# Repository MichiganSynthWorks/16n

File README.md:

# 16n Fader Bank

Credits
Based on original work by Brian Crabtree and Sean Hellfritsch.
Minijack MIDI, I2C circuitry and CV outputs by Tom Armitage.
Firmware by Brian Crabtree, Tom Armitage, and Brendon Cassidy.

https://github.com/16n-faderbank/16n

License
=======

Code (AVR projects): GPL3.0.

Code: MIT license.

Hardware: cc-by-sa-4.0

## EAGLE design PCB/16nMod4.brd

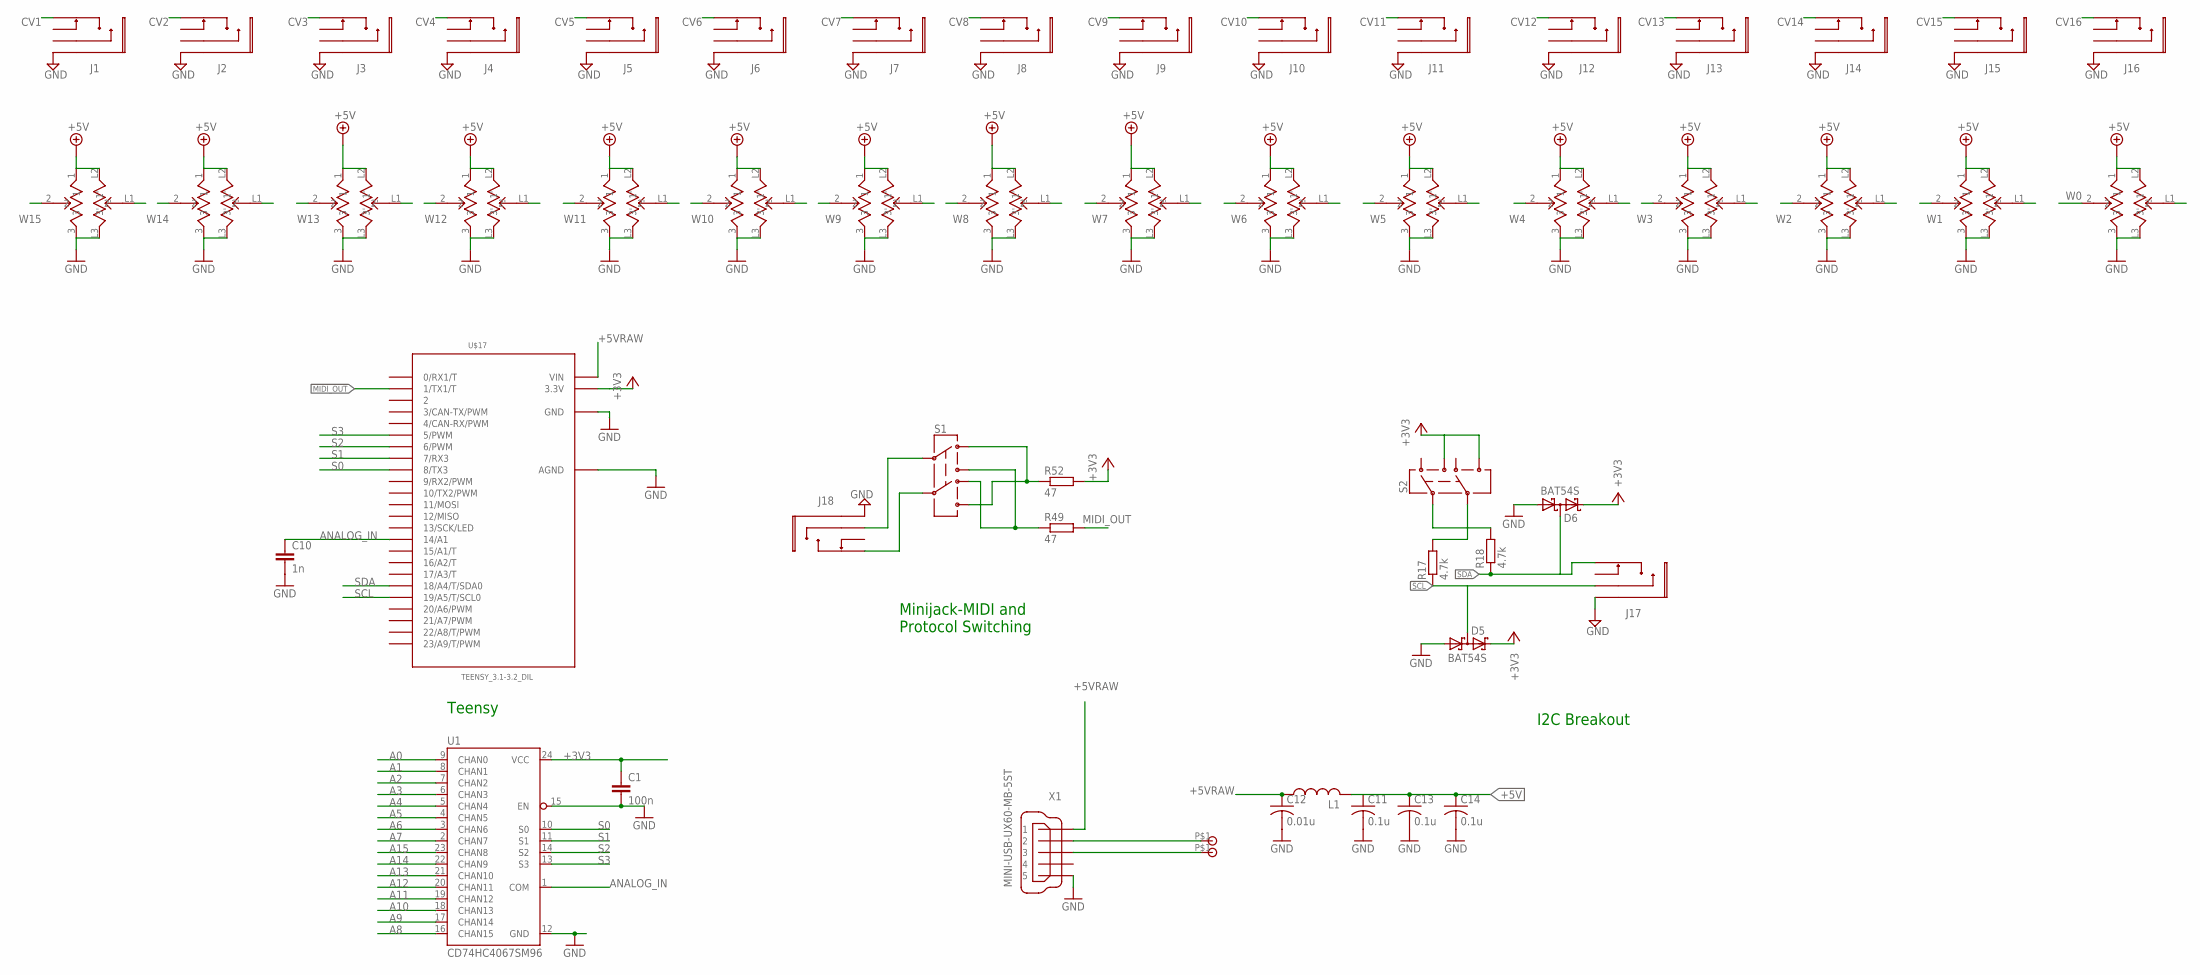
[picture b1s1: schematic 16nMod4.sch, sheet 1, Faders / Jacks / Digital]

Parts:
C1: 100n; C0805
C10: 1n; C0805
C11, C13, C14: 0.1u; C0805K
C12: 0.01u; C0805K
D5, D6: BAT54S; SOT23
J1, J2, J3, J4, J5, J6, J7, J8, J9, J10, J11, J12, J13, J14, J15, J16, J17, J18: PJ327E; PJ327
L1: L-USL2012C; L2012C
R17, R18: 4.7k; R0805
R49, R52: 47; R0805
S1, S2: SWITCH-DPDT; JS202011JAQN
U1: CD74HC4067SM96; SOIC127P1030X265-24
U$1, U$2, U$3, U$4, U$5, U$6, U$7, U$8, U$9, U$10, U$11, U$12, U$13, U$14, U$15, U$16: SLIDEPOT-ALPS-60MM; RS6011SP600
U$17: TEENSY_3.1-3.2_DIL; TEENSY_3.0-3.2&LC_DIL
U$19, U$20: POGO1X; POGO2MM
X1: MINI-USB-UX60-MB-5ST; UX60-MB-5ST

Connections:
+3V3: C1.1, D5.2, D6.2, R52.2, S2.P$3 (6), S2.P$7 (3), U1.24 (VCC), U$17.3.3V
+5V: C11.1, C13.1, C14.1, L1.2, U$1.1, U$1.L2 (1'), U$2.1, U$2.L2 (1'), U$3.1, U$3.L2 (1'), U$4.1, U$4.L2 (1'), U$5.1, U$5.L2 (1'), U$6.1, U$6.L2 (1'), U$7.1, U$7.L2 (1'), U$8.1, U$8.L2 (1'), U$9.1, U$9.L2 (1'), U$10.1, U$10.L2 (1'), U$11.1, U$11.L2 (1'), U$12.1, U$12.L2 (1'), U$13.1, U$13.L2 (1'), U$14.1, U$14.L2 (1'), U$15.1, U$15.L2 (1'), U$16.1, U$16.L2 (1'); also elsewhere on the board
+5VRAW: C12.1, L1.1, U$17.VIN, X1.1
A0: U1.9 (CHAN0); also elsewhere on the board
A1: U1.8 (CHAN1); also elsewhere on the board
A2: U1.7 (CHAN2); also elsewhere on the board
A3: U1.6 (CHAN3); also elsewhere on the board
A4: U1.5 (CHAN4); also elsewhere on the board
A5: U1.4 (CHAN5); also elsewhere on the board
A6: U1.3 (CHAN6); also elsewhere on the board
A7: U1.2 (CHAN7); also elsewhere on the board
A8: U1.16 (CHAN15); also elsewhere on the board
A9: U1.17 (CHAN14); also elsewhere on the board
A10: U1.18 (CHAN13); also elsewhere on the board
A11: U1.19 (CHAN12); also elsewhere on the board
A12: U1.20 (CHAN11); also elsewhere on the board
A13: U1.21 (CHAN10); also elsewhere on the board
A14: U1.22 (CHAN9); also elsewhere on the board
A15: U1.23 (CHAN8); also elsewhere on the board
ANALOG_IN: C10.1, U1.1 (COM), U$17.14/A0 (14/A1)
CV1: J1.P$2; also elsewhere on the board
CV2: J2.P$2; also elsewhere on the board
CV3: J3.P$2; also elsewhere on the board
CV4: J4.P$2; also elsewhere on the board
CV5: J5.P$2; also elsewhere on the board
CV6: J6.P$2; also elsewhere on the board
CV7: J7.P$2; also elsewhere on the board
CV8: J8.P$2; also elsewhere on the board
CV9: J9.P$2; also elsewhere on the board
CV10: J10.P$2; also elsewhere on the board
CV11: J11.P$2; also elsewhere on the board
CV12: J12.P$2; also elsewhere on the board
CV13: J13.P$2; also elsewhere on the board
CV14: J14.P$2; also elsewhere on the board
CV15: J15.P$2; also elsewhere on the board
CV16: J16.P$2; also elsewhere on the board
D+: U$20.P$1, X1.3
D-: U$19.P$1, X1.2
GND: C1.2, C10.2, C11.2, C12.2, C13.2, C14.2, D5.3 (1), D6.3 (1), J1.P$1, J2.P$1, J3.P$1, J4.P$1, J5.P$1, J6.P$1, J7.P$1, J8.P$1, J9.P$1, J10.P$1, J11.P$1, J12.P$1, J13.P$1, J14.P$1, J15.P$1, J16.P$1, J17.P$1, J18.P$1, U1.12 (GND), U1.15 (EN), U$1.3, U$1.L3 (3'), U$2.3, U$2.L3 (3'), U$3.3, U$3.L3 (3'), U$4.3, U$4.L3 (3'), U$5.3, U$5.L3 (3'), U$6.3, U$6.L3 (3'), U$7.3, U$7.L3 (3'), U$8.3, U$8.L3 (3'), U$9.3, U$9.L3 (3'), U$10.3, U$10.L3 (3'), U$11.3, U$11.L3 (3'), U$12.3, U$12.L3 (3'), U$13.3, U$13.L3 (3'), U$14.3, U$14.L3 (3'), U$15.3, U$15.L3 (3'), U$16.3, U$16.L3 (3'), U$17.AGND, U$17.GND, X1.5; also elsewhere on the board
MIDI_OUT: R49.2, U$17.1 (1/TX1/T)
unnamed: J18.P$2, S1.P$2 (5)
unnamed: J18.P$3, S1.P$6 (2)
unnamed: R49.1, S1.P$1 (4), S1.P$7 (3)
unnamed: R52.1, S1.P$3 (6), S1.P$5 (1)
unnamed: R17.2, S2.P$2 (5)
unnamed: R18.2, S2.P$6 (2)
S0: U1.10 (S0), U$17.8 (8/TX3)
S1: U1.11 (S1), U$17.7 (7/RX3)
S2: U1.14 (S2), U$17.6 (6/PWM)
S3: U1.13 (S3), U$17.5 (5/PWM)
SCL: D5.1 (3), J17.P$3, R17.1, U$17.19/A5 (19/A5/T/SCL0)
SDA: D6.1 (3), J17.P$2, R18.1, U$17.18/A4 (18/A4/T/SDA0)
W0: U$1.2, U$1.L1 (2'); also elsewhere on the board
W1: U$2.2, U$2.L1 (2'); also elsewhere on the board
W2: U$3.2, U$3.L1 (2'); also elsewhere on the board
W3: U$4.2, U$4.L1 (2'); also elsewhere on the board
W4: U$5.2, U$5.L1 (2'); also elsewhere on the board
W5: U$6.2, U$6.L1 (2'); also elsewhere on the board
W6: U$7.2, U$7.L1 (2'); also elsewhere on the board
W7: U$8.2, U$8.L1 (2'); also elsewhere on the board
W8: U$9.2, U$9.L1 (2'); also elsewhere on the board
W9: U$10.2, U$10.L1 (2'); also elsewhere on the board
W10: U$11.2, U$11.L1 (2'); also elsewhere on the board
W11: U$12.2, U$12.L1 (2'); also elsewhere on the board
W12: U$13.2, U$13.L1 (2'); also elsewhere on the board
W13: U$14.2, U$14.L1 (2'); also elsewhere on the board
W14: U$15.2, U$15.L1 (2'); also elsewhere on the board
W15: U$16.2, U$16.L1 (2'); also elsewhere on the board

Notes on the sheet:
Teensy
Minijack-MIDI and Protocol Switching
I2C Breakout

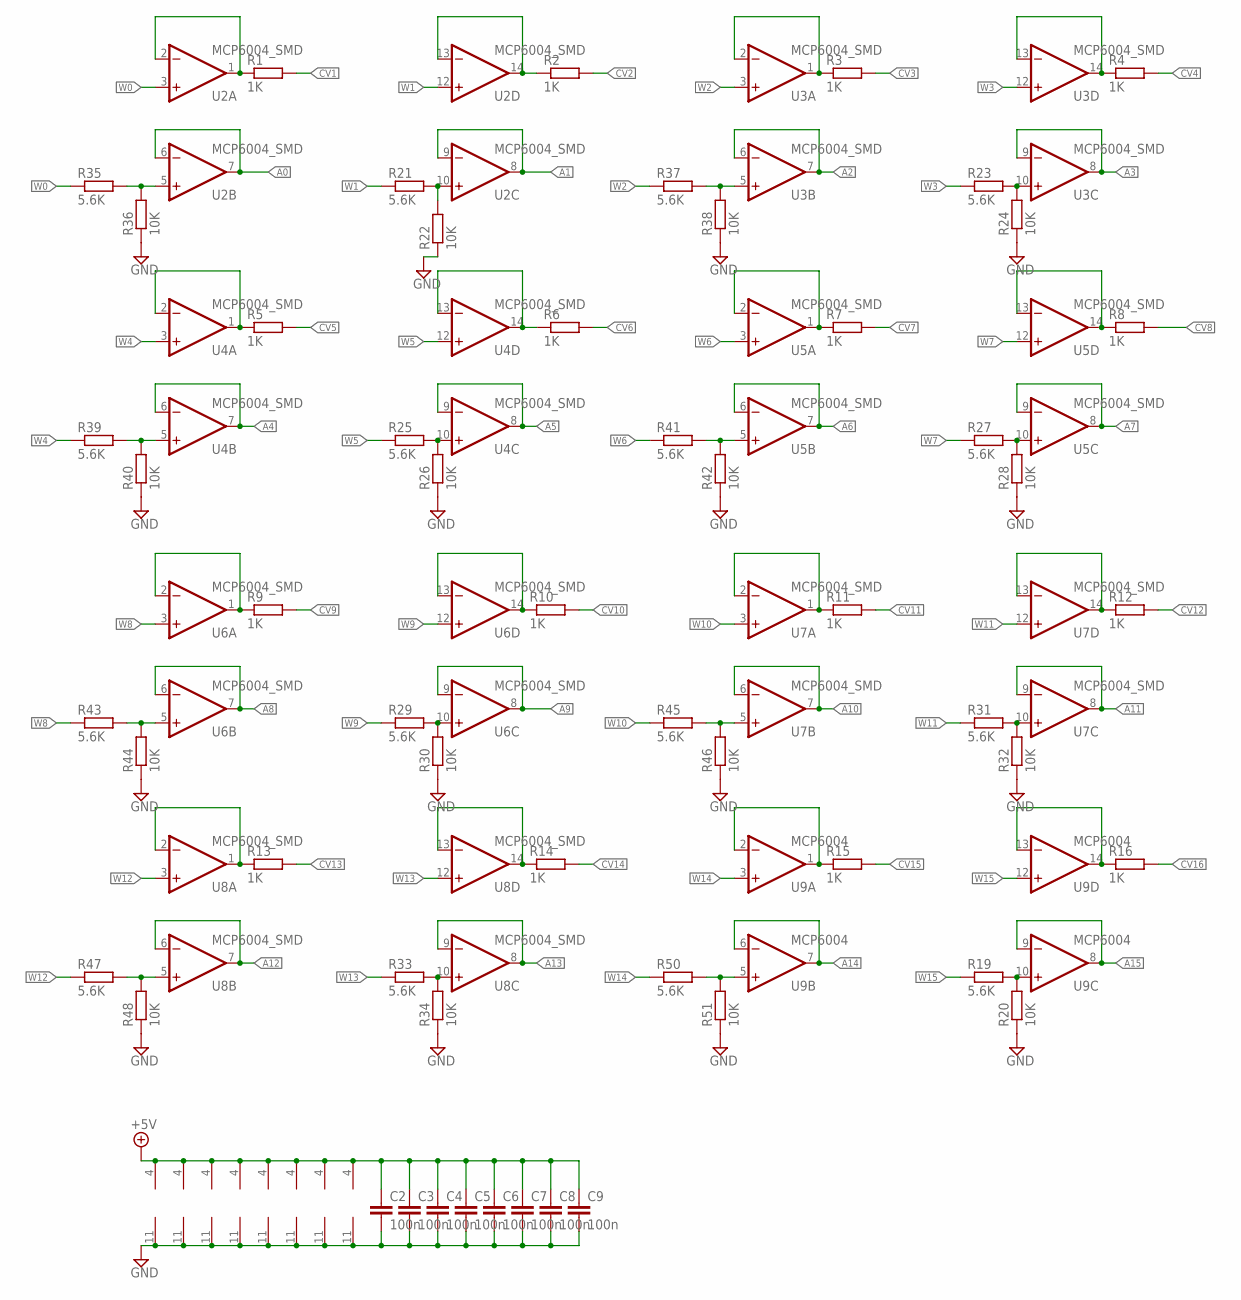
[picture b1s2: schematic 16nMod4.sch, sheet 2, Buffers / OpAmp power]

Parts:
C2, C3, C4, C5, C6, C7, C8, C9: 100n; C0805
R1, R2, R3, R4, R5, R6, R7, R8, R9, R10, R11, R12, R13, R14, R15, R16: 1K; R0805
R19, R21, R23, R25, R27, R29, R31, R33, R35, R37, R39, R41, R43, R45, R47, R50: 5.6K; R0805
R20, R22, R24, R26, R28, R30, R32, R34, R36, R38, R40, R42, R44, R46, R48, R51: 10K; R0805
U2, U3, U4, U5, U6, U7, U8: MCP6004_SMD; SO14
U9: MCP6004; SO14

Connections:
+5V: C2.1, C3.1, C4.1, C5.1, C6.1, C7.1, C8.1, C9.1, U2.4 (V+), U3.4 (V+), U4.4 (V+), U5.4 (V+), U6.4 (V+), U7.4 (V+), U8.4 (V+), U9.4 (V+); also elsewhere on the board
A0: U2.6 (-IN), U2.7 (OUT); also elsewhere on the board
A1: U2.8 (OUT), U2.9 (-IN); also elsewhere on the board
A2: U3.6 (-IN), U3.7 (OUT); also elsewhere on the board
A3: U3.8 (OUT), U3.9 (-IN); also elsewhere on the board
A4: U4.6 (-IN), U4.7 (OUT); also elsewhere on the board
A5: U4.8 (OUT), U4.9 (-IN); also elsewhere on the board
A6: U5.6 (-IN), U5.7 (OUT); also elsewhere on the board
A7: U5.8 (OUT), U5.9 (-IN); also elsewhere on the board
A8: U6.6 (-IN), U6.7 (OUT); also elsewhere on the board
A9: U6.8 (OUT), U6.9 (-IN); also elsewhere on the board
A10: U7.6 (-IN), U7.7 (OUT); also elsewhere on the board
A11: U7.8 (OUT), U7.9 (-IN); also elsewhere on the board
A12: U8.6 (-IN), U8.7 (OUT); also elsewhere on the board
A13: U8.8 (OUT), U8.9 (-IN); also elsewhere on the board
A14: U9.6 (-IN), U9.7 (OUT); also elsewhere on the board
A15: U9.8 (OUT), U9.9 (-IN); also elsewhere on the board
CV1: R1.2; also elsewhere on the board
CV2: R2.2; also elsewhere on the board
CV3: R3.2; also elsewhere on the board
CV4: R4.2; also elsewhere on the board
CV5: R5.2; also elsewhere on the board
CV6: R6.2; also elsewhere on the board
CV7: R7.2; also elsewhere on the board
CV8: R8.2; also elsewhere on the board
CV9: R9.2; also elsewhere on the board
CV10: R10.2; also elsewhere on the board
CV11: R11.2; also elsewhere on the board
CV12: R12.2; also elsewhere on the board
CV13: R13.2; also elsewhere on the board
CV14: R14.2; also elsewhere on the board
CV15: R15.2; also elsewhere on the board
CV16: R16.2; also elsewhere on the board
GND: C2.2, C3.2, C4.2, C5.2, C6.2, C7.2, C8.2, C9.2, R20.1, R22.1, R24.1, R26.1, R28.1, R30.1, R32.1, R34.1, R36.1, R38.1, R40.1, R42.1, R44.1, R46.1, R48.1, R51.1, U2.11 (V-), U3.11 (V-), U4.11 (V-), U5.11 (V-), U6.11 (V-), U7.11 (V-), U8.11 (V-), U9.11 (V-); also elsewhere on the board
unnamed: R37.2, R38.2, U3.5 (+IN)
unnamed: R23.2, R24.2, U3.10 (+IN)
unnamed: R35.2, R36.2, U2.5 (+IN)
unnamed: R21.2, R22.2, U2.10 (+IN)
unnamed: R39.2, R40.2, U4.5 (+IN)
unnamed: R25.2, R26.2, U4.10 (+IN)
unnamed: R41.2, R42.2, U5.5 (+IN)
unnamed: R27.2, R28.2, U5.10 (+IN)
unnamed: R43.2, R44.2, U6.5 (+IN)
unnamed: R29.2, R30.2, U6.10 (+IN)
unnamed: R45.2, R46.2, U7.5 (+IN)
unnamed: R31.2, R32.2, U7.10 (+IN)
unnamed: R47.2, R48.2, U8.5 (+IN)
unnamed: R33.2, R34.2, U8.10 (+IN)
unnamed: R50.2, R51.2, U9.5 (+IN)
unnamed: R19.2, R20.2, U9.10 (+IN)
unnamed: R1.1, U2.1 (OUT), U2.2 (-IN)
unnamed: R2.1, U2.13 (-IN), U2.14 (OUT)
unnamed: R3.1, U3.1 (OUT), U3.2 (-IN)
unnamed: R4.1, U3.13 (-IN), U3.14 (OUT)
unnamed: R5.1, U4.1 (OUT), U4.2 (-IN)
unnamed: R6.1, U4.13 (-IN), U4.14 (OUT)
unnamed: R7.1, U5.1 (OUT), U5.2 (-IN)
unnamed: R8.1, U5.13 (-IN), U5.14 (OUT)
unnamed: R9.1, U6.1 (OUT), U6.2 (-IN)
unnamed: R10.1, U6.13 (-IN), U6.14 (OUT)
unnamed: R11.1, U7.1 (OUT), U7.2 (-IN)
unnamed: R12.1, U7.13 (-IN), U7.14 (OUT)
unnamed: R13.1, U8.1 (OUT), U8.2 (-IN)
unnamed: R14.1, U8.13 (-IN), U8.14 (OUT)
unnamed: R15.1, U9.1 (OUT), U9.2 (-IN)
unnamed: R16.1, U9.13 (-IN), U9.14 (OUT)
W0: R35.1, U2.3 (+IN); also elsewhere on the board
W1: R21.1, U2.12 (+IN); also elsewhere on the board
W2: R37.1, U3.3 (+IN); also elsewhere on the board
W3: R23.1, U3.12 (+IN); also elsewhere on the board
W4: R39.1, U4.3 (+IN); also elsewhere on the board
W5: R25.1, U4.12 (+IN); also elsewhere on the board
W6: R41.1, U5.3 (+IN); also elsewhere on the board
W7: R27.1, U5.12 (+IN); also elsewhere on the board
W8: R43.1, U6.3 (+IN); also elsewhere on the board
W9: R29.1, U6.12 (+IN); also elsewhere on the board
W10: R45.1, U7.3 (+IN); also elsewhere on the board
W11: R31.1, U7.12 (+IN); also elsewhere on the board
W12: R47.1, U8.3 (+IN); also elsewhere on the board
W13: R33.1, U8.12 (+IN); also elsewhere on the board
W14: R50.1, U9.3 (+IN); also elsewhere on the board
W15: R19.1, U9.12 (+IN); also elsewhere on the board

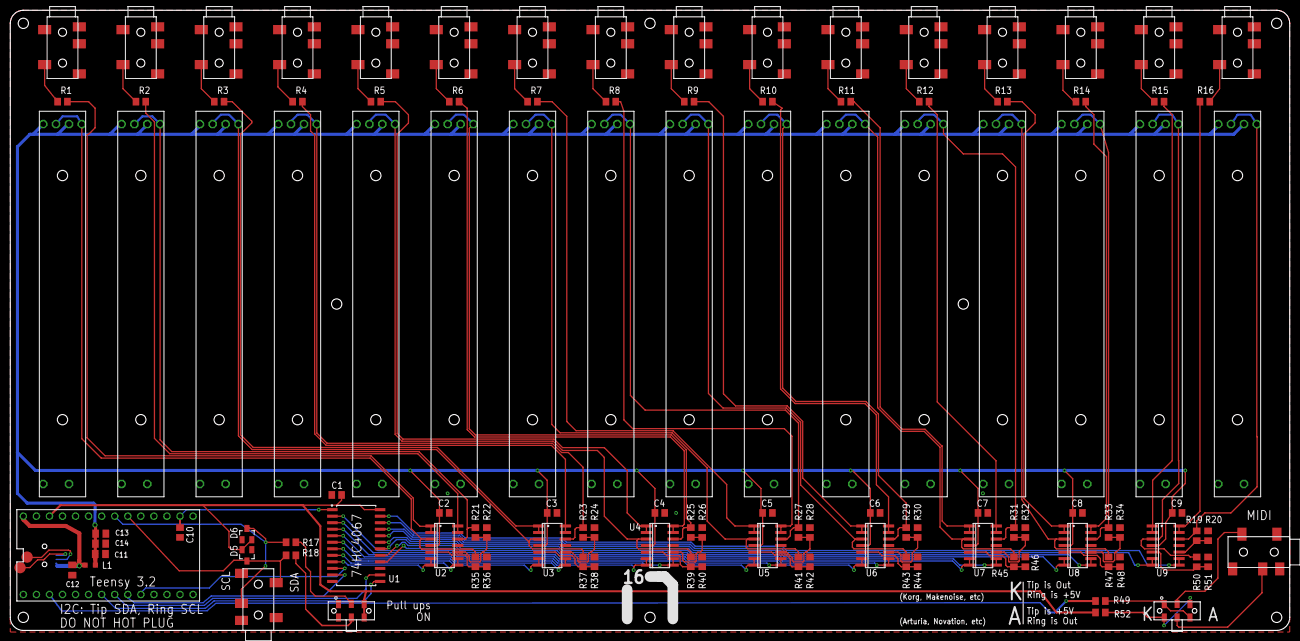
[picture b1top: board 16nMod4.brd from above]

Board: 2 copper layers, 248.9 x 120.7 mm, 118 parts (1 on the bottom side), 100 nets.

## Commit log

2020-04-06 intial release

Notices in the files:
PCB/16nMod4.brd:
Creative Commons
Attribution / ShareAlike
parts and their libraries:
SparkFun-Electromechanical: Licensing: Creative Commons ShareAlike 4.0 International - https://creativecommons.org/licenses/by-sa/4.0
